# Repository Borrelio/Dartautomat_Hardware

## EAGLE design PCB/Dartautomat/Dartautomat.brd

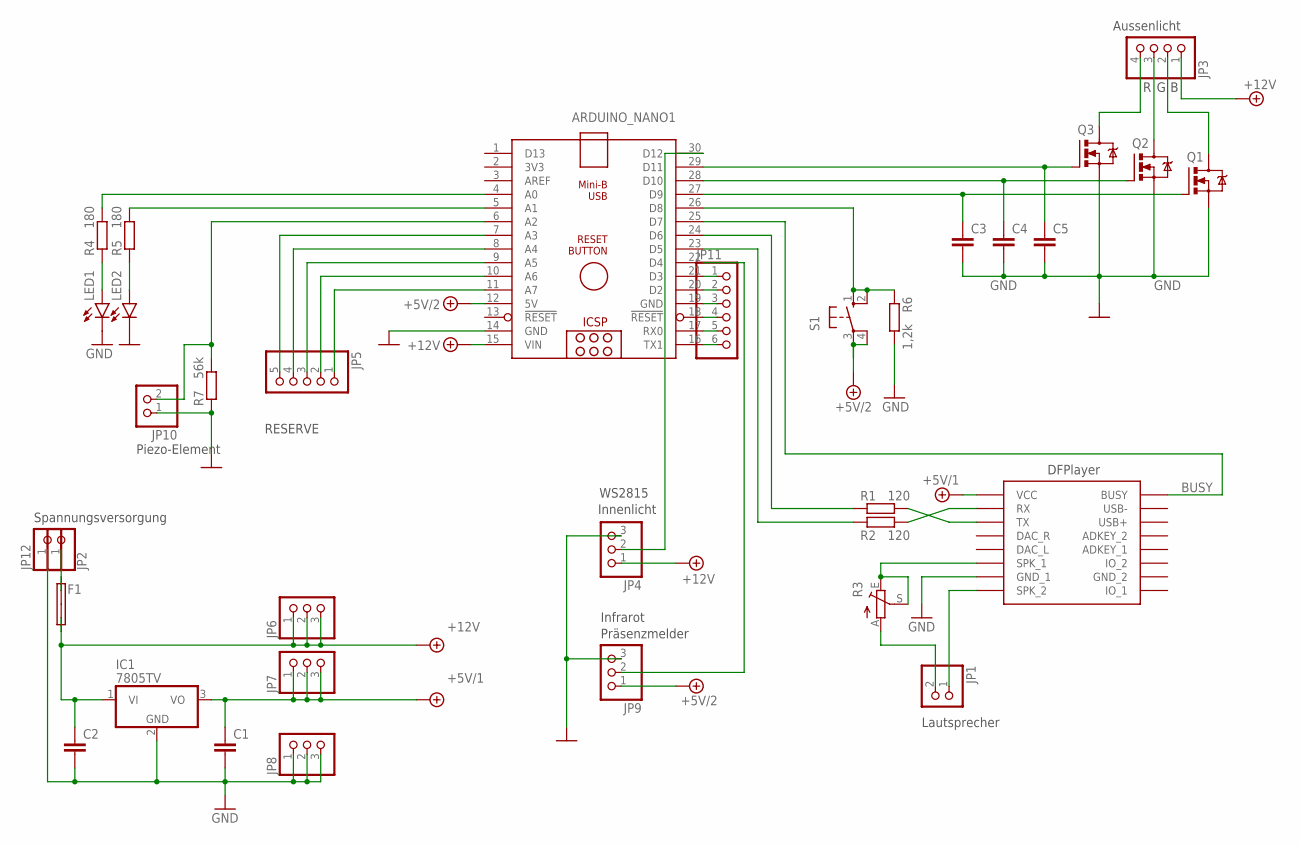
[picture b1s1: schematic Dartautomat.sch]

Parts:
ARDUINO_NANO1: ARDUINO_NANO
C1, C2, C3, C4, C5: C-EU050-045X075; C050-045X075
F1: SHK20L
IC1: 7805TV; TO220V
JP1, JP10: PINHD-1X2; 1X02
JP2, JP12: PINHD-1X1; 1X01
JP3: PINHD-1X4; 1X04
JP4, JP6, JP7, JP8, JP9: PINHD-1X3; 1X03
JP5: PINHD-1X5; 1X05
JP11: PINHD-1X6; 1X06
LED1, LED2: LED3MM
Q1, Q2, Q3: IRLZ44ZNEU; TO220BV
R1, R2: 120; 0207/10
R3: TRIM_EU-CA6H; CA6H
R4, R5: 180; 0207/12
R6: 1,2k; 0207/12
R7: 56k; 0207/12
S1: 10-XX; B3F-10XX
U$1: DFPLAYER

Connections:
+5V/1: C1.1, IC1.3 (VO), JP7.1, JP7.2, JP7.3, U$1.VCC
+5V/2: ARDUINO_NANO1.12 (5V), JP9.1, S1.3, S1.4 (P1)
+12V: ARDUINO_NANO1.15 (VIN), C2.1, F1.1A, F1.1B, IC1.1 (VI), JP3.1, JP4.1, JP6.1, JP6.2, JP6.3
BUSY: ARDUINO_NANO1.25 (D7), U$1.BUSY
GND: ARDUINO_NANO1.14 (GND), C1.2, C2.2, C3.2, C4.2, C5.2, IC1.2 (GND), JP4.3, JP8.1, JP8.2, JP8.3, JP9.3, JP10.1, JP12.1, LED1.K (C), LED2.K (C), Q1.S, Q2.S, Q3.S, R6.2, R7.1, U$1.GND_1
unnamed: ARDUINO_NANO1.30 (D12), JP4.2
unnamed: R2.2, U$1.RX
unnamed: ARDUINO_NANO1.29 (D11), C5.1, Q3.G
unnamed: R1.2, U$1.TX
unnamed: JP1.2, R3.A
unnamed: JP1.1, U$1.SPK2 (SPK_2)
unnamed: R3.E, R3.S, U$1.SPK1 (SPK_1)
unnamed: JP3.3, Q2.D
unnamed: ARDUINO_NANO1.23 (D5), R2.1
unnamed: ARDUINO_NANO1.21 (D3), JP11.1
unnamed: JP3.2, Q1.D
unnamed: JP3.4, Q3.D
unnamed: ARDUINO_NANO1.24 (D6), R1.1
unnamed: ARDUINO_NANO1.20 (D2), JP11.2
unnamed: LED1.A, R4.1
unnamed: LED2.A, R5.1
unnamed: ARDUINO_NANO1.5 (A1), R5.2
unnamed: ARDUINO_NANO1.4 (A0), R4.2
unnamed: ARDUINO_NANO1.11 (A7), JP5.1
unnamed: ARDUINO_NANO1.10 (A6), JP5.2
unnamed: ARDUINO_NANO1.9 (A5), JP5.3
unnamed: ARDUINO_NANO1.8 (A4), JP5.4
unnamed: ARDUINO_NANO1.7 (A3), JP5.5
unnamed: ARDUINO_NANO1.6 (A2), JP10.2, R7.2
unnamed: ARDUINO_NANO1.22 (D4), JP9.2
unnamed: ARDUINO_NANO1.26 (D8), R6.1, S1.1 (S), S1.2 (S1)
unnamed: F1.2A, F1.2B, JP2.1
unnamed: ARDUINO_NANO1.19 (GND), JP11.3
unnamed: ARDUINO_NANO1.18 (!RESET), JP11.4
unnamed: ARDUINO_NANO1.17 (RX0), JP11.5
unnamed: ARDUINO_NANO1.27 (D9), C3.1, Q1.G
unnamed: ARDUINO_NANO1.16 (TX1), JP11.6
unnamed: ARDUINO_NANO1.28 (D10), C4.1, Q2.G

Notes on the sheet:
Aussenlicht
Lautsprecher
DFPlayer
Innenlicht
WS2815
Infrarot
Präsenzmelder
Piezo-Element
RESERVE
Spannungsversorgung

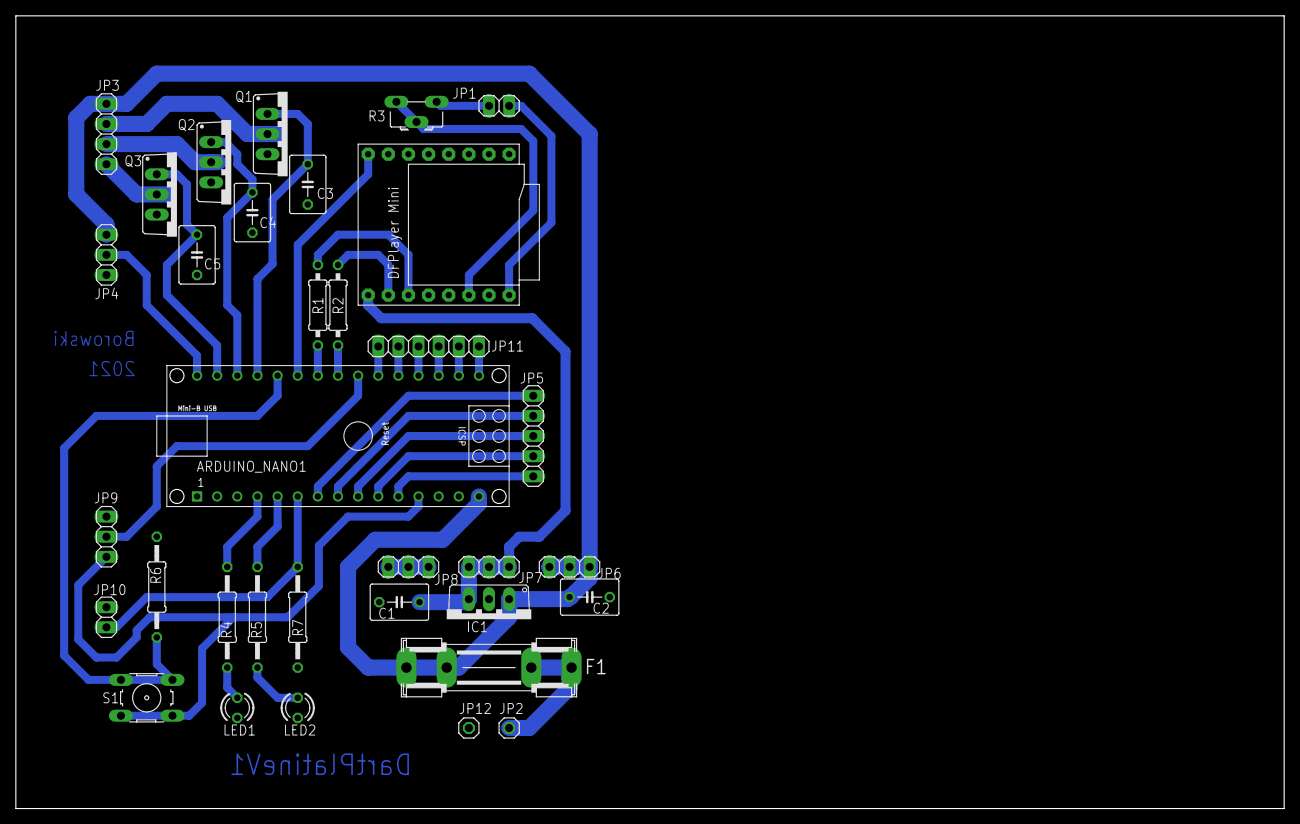
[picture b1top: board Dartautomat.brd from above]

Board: 2 copper layers, 160.0 x 100.0 mm, 34 parts (0 on the bottom side), 38 nets.

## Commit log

2022-02-28 Erste Version der Strukturierung am DFPlayer
